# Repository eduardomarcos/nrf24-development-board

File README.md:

# NRF24 Development Board

The goal of this repository is to keep a version of a useful development boards for my [MySensors](https://www.mysensors.org/) projects based on atmega 328, esp32 and nrf24l01 module, so I do not need to wire all componentes into a breadboard.

## Atmega328 Development Board

Features:
* Almost all I/O pins available for direct connection
* Uses [3.3V Boost Buck](https://es.aliexpress.com/item/32822323191.html) for an input up to 5V (Considering that the sensor will be powered by a [TP4056](https://www.best-microcontroller-projects.com/tp4056.html) battery charger)
* If voltage regulator is wired by a connector headers instead of soldering, it would be possible to use a different voltage regulator (keep in mind that nrf24 module works with no more than ~3.6V or could be damaged)
* Internal voltage of 3.3 for the atmega 328
* NRF24L01 wired with a 10uF capacitor for noise reduction
* Reset button
* On board jumpers to disable 16 MHz crystal (and use internal 8 MHz from atmega 328)

This is the way it looks like:

## Esp32 Development Board

Features:
* All I/O pins available for direct connection
* NRF24L01 wired with an optional capacitor for noise reduction
* Err Tx and Rx led diodes for mysensors capability

This is the way it looks like:

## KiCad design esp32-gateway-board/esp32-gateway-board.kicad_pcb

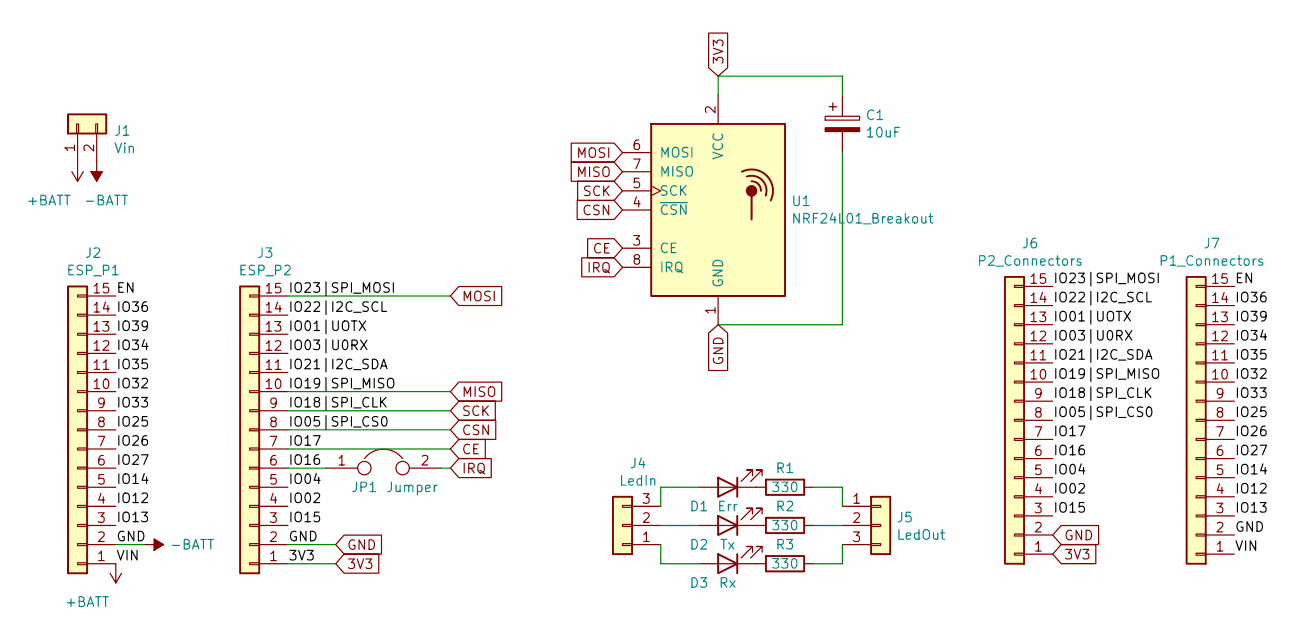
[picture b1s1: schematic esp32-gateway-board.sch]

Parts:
C1: 10uF; PinSocket_1x02_P2.54mm_Vertical
D1: Err; LED_D3.0mm
D2: Tx; LED_D3.0mm
D3: Rx; LED_D3.0mm
J1: Vin; PinSocket_1x02_P2.54mm_Vertical
J2: ESP_P1; PinSocket_1x15_P2.54mm_Vertical
J3: ESP_P2; PinSocket_1x15_P2.54mm_Vertical
J4: LedIn; PinSocket_1x03_P2.54mm_Vertical
J5: LedOut; PinSocket_1x03_P2.54mm_Vertical
J6: P2_Connectors; PinSocket_1x15_P2.54mm_Vertical
J7: P1_Connectors; PinSocket_1x15_P2.54mm_Vertical
JP1: Jumper; PinHeader_1x02_P2.54mm_Vertical
R1, R2, R3: 330; R_Axial_DIN0207_L6.3mm_D2.5mm_P10.16mm_Horizontal
U1: NRF24L01_Breakout; nRF24L01_Breakout

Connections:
3V3: C1.1, J3.1, J6.1, U1.2 (VCC)
+BATT: J1.1, J2.1, J7.1
/EN: J2.15, J7.15
/IO01|UOTX: J3.13, J6.13
/IO02: J3.4, J6.4
/IO03|U0RX: J3.12, J6.12
/IO04: J3.5, J6.5
/IO12: J2.4, J7.4
/IO13: J2.3, J7.3
/IO14: J2.5, J7.5
/IO15: J3.3, J6.3
/IO16: J3.6, J6.6, JP1.1
/IO21|I2C_SDA: J3.11, J6.11
/IO22|I2C_SCL: J3.14, J6.14
/IO25: J2.8, J7.8
/IO26: J2.7, J7.7
/IO27: J2.6, J7.6
/IO32: J2.10, J7.10
/IO33: J2.9, J7.9
/IO34: J2.12, J7.12
/IO35: J2.11, J7.11
/IO36: J2.14, J7.14
/IO39: J2.13, J7.13
CE: J3.7, J6.7, U1.3 (CE)
CSN: J3.8, J6.8, U1.4 (~CSN)
GND: C1.2, J1.2, J2.2, J3.2, J6.2, J7.2, U1.1 (GND)
MISO: J3.10, J6.10, U1.7 (MISO)
MOSI: J3.15, J6.15, U1.6 (MOSI)
unnamed: D1.1 (K), R1.2
unnamed: D1.2 (A), J4.3
unnamed: D2.1 (K), R2.2
unnamed: D2.2 (A), J4.2
unnamed: D3.1 (K), R3.2
unnamed: D3.2 (A), J4.1
unnamed: J5.1, R1.1
unnamed: J5.2, R2.1
unnamed: J5.3, R3.1
unnamed: JP1.2, U1.8 (IRQ)
SCK: J3.9, J6.9, U1.5 (SCK)

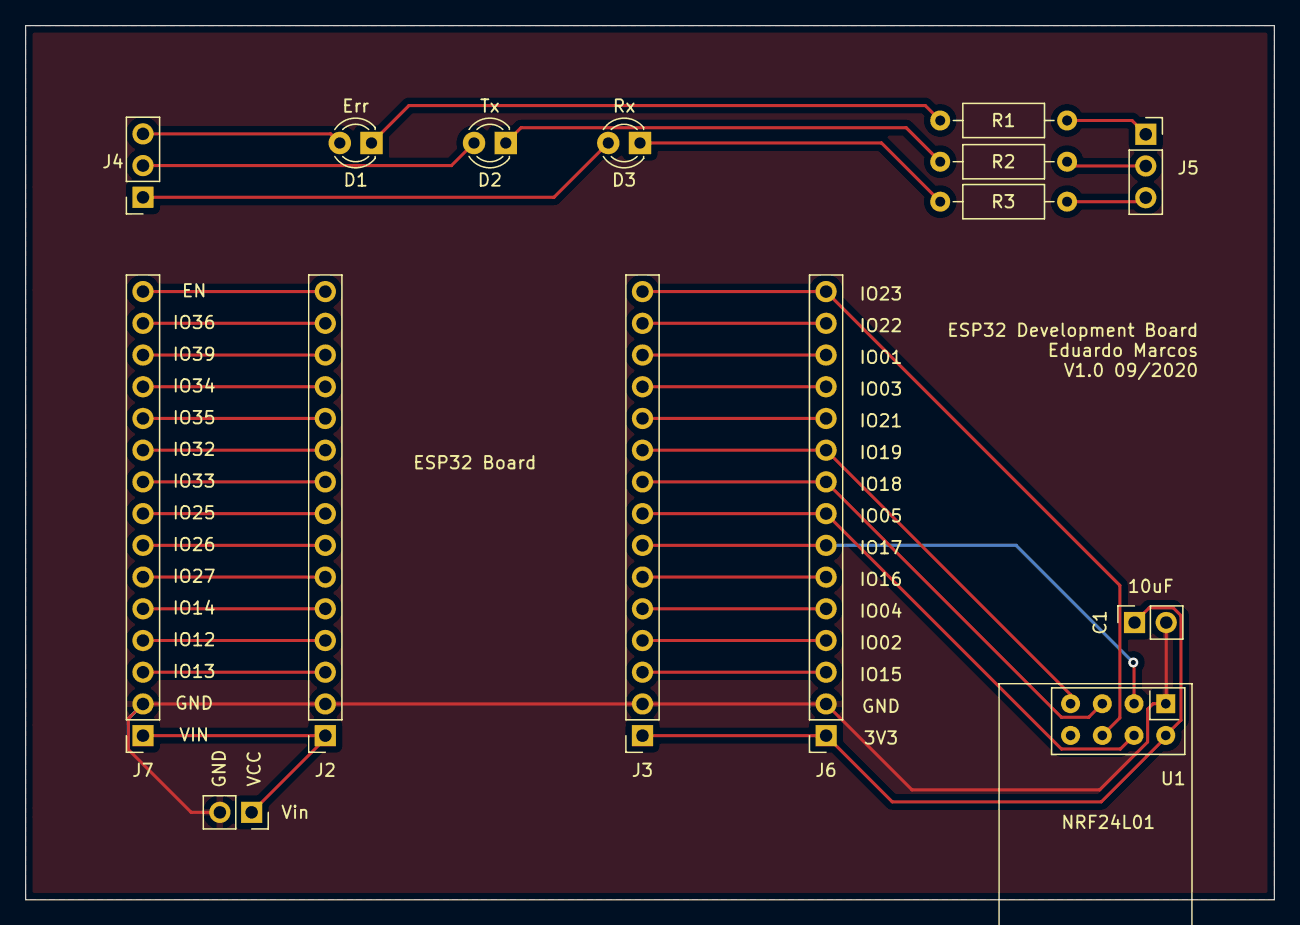
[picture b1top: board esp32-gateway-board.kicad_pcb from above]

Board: 2 copper layers, 100.0 x 70.0 mm, 15 parts (0 on the bottom side), 38 nets.

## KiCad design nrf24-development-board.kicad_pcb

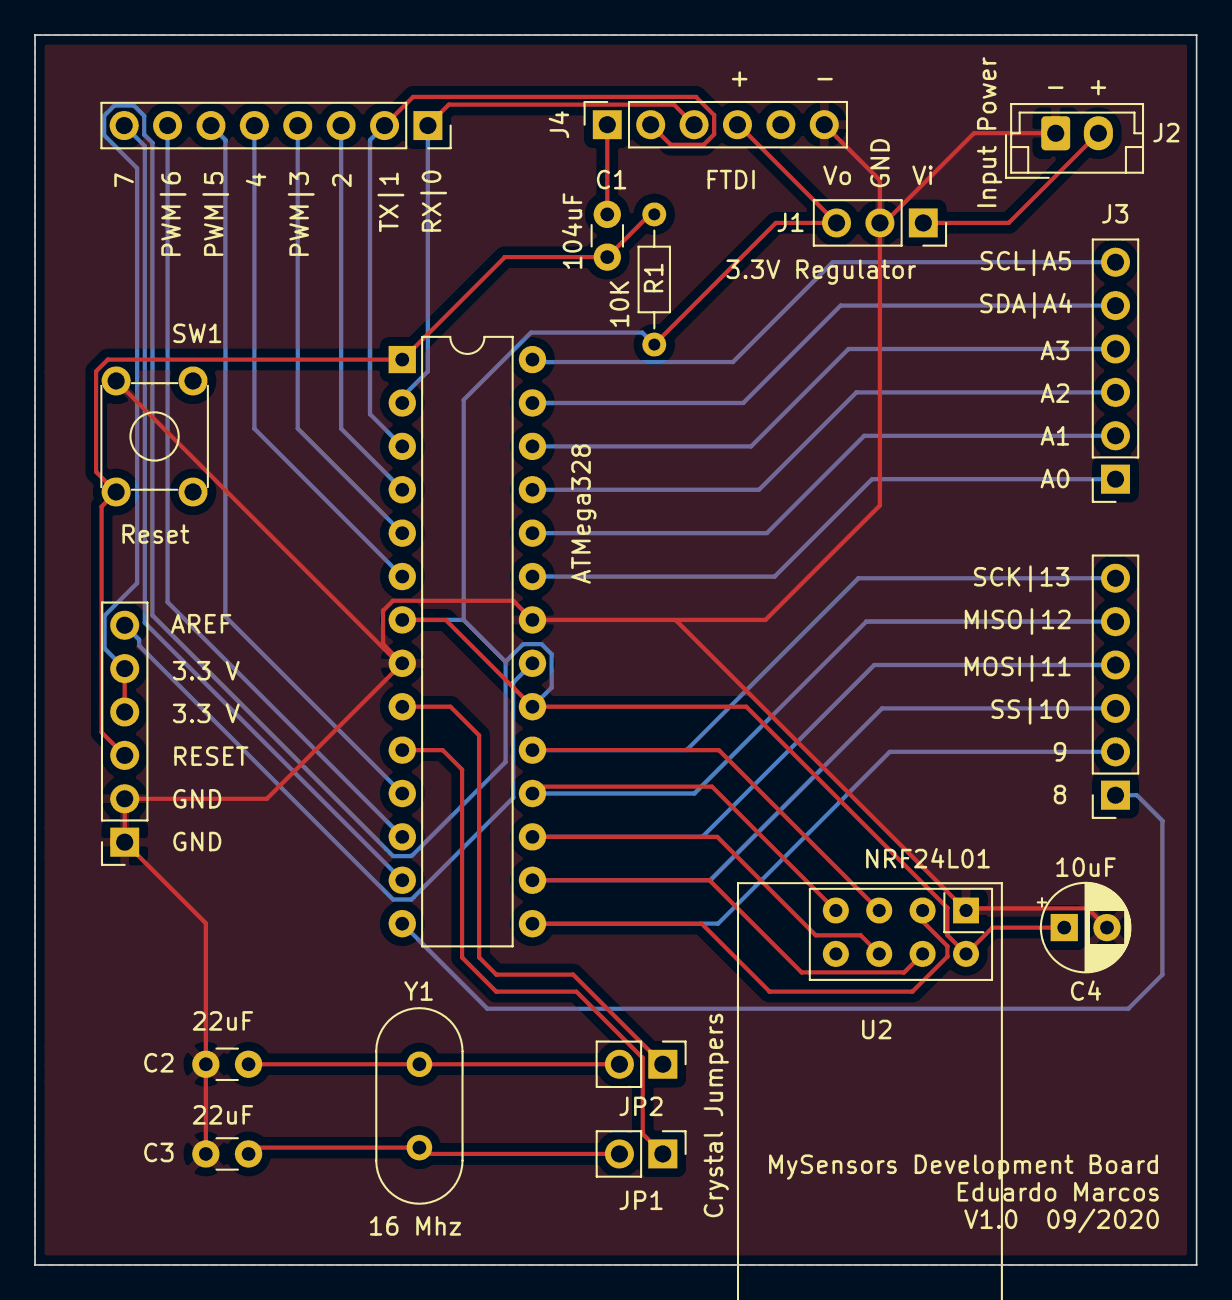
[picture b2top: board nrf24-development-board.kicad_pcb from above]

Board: 2 copper layers, 68.0 x 72.0 mm, 18 parts (0 on the bottom side), 29 nets.

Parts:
ATMega328: ATmega328P-PU; DIP-28_W7.62mm
C1: 104uF; C_Disc_D3.0mm_W1.6mm_P2.50mm
C2, C3: 22uF; C_Disc_D3.0mm_W1.6mm_P2.50mm
C4: 10uF; CP_Radial_D5.0mm_P2.50mm
J1: 3.3V Regulator; PinSocket_1x03_P2.54mm_Vertical
J2: Vin; JST_EH_B2B-EH-A_1x02_P2.50mm_Vertical
J3: Analog Connectors; PinSocket_1x06_P2.54mm_Vertical
J4: FTDI; PinSocket_1x06_P2.54mm_Vertical
J5: Digital Connectors; PinSocket_1x06_P2.54mm_Vertical
J6: Digital Connectors; PinSocket_1x08_P2.54mm_Vertical
J7: Control Connectors; PinSocket_1x06_P2.54mm_Vertical
JP1, JP2: Jumper; PinHeader_1x02_P2.54mm_Vertical
R1: 10K; R_Axial_DIN0204_L3.6mm_D1.6mm_P7.62mm_Horizontal
SW1: Reset; SW_TH_Tactile_Omron_B3F-10xx
U2: NRF24L01; nRF24L01_Breakout
Y1: 16Mhz; Crystal_HC49-4H_Vertical

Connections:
+3V3: ATMega328.7, ATMega328.20, C4.1, J1.3, J4.4, J7.4, J7.5, R1.2, U2.2
/Aref: ATMega328.21, J7.6
/DTR: C1.1, J4.1
/Rx: ATMega328.2, ATMega328.3, J4.2, J4.3, J6.1, J6.2
GND: ATMega328.8, ATMega328.22, C2.1, C3.1, C4.2, J1.2, J2.1, J4.6, J7.1, J7.2, SW1.2, U2.1
unnamed: ATMega328.1, C1.2, J7.3, R1.1, SW1.1
unnamed: ATMega328.4, J6.3
unnamed: ATMega328.5, J6.4
unnamed: ATMega328.6, J6.5
unnamed: ATMega328.9, JP2.1
unnamed: ATMega328.10, JP1.1
unnamed: ATMega328.11, J6.6
unnamed: ATMega328.12, J6.7
unnamed: ATMega328.13, J6.8
unnamed: ATMega328.14, J5.1
unnamed: ATMega328.15, J5.2, U2.3
unnamed: ATMega328.16, J5.3, U2.4
unnamed: ATMega328.17, J5.4, U2.6
unnamed: ATMega328.18, J5.5, U2.7
unnamed: ATMega328.19, J5.6, U2.5
unnamed: ATMega328.23, J3.1
unnamed: ATMega328.24, J3.2
unnamed: ATMega328.25, J3.3
unnamed: ATMega328.26, J3.4
unnamed: ATMega328.27, J3.5
unnamed: ATMega328.28, J3.6
unnamed: C2.2, JP2.2, Y1.1
unnamed: C3.2, JP1.2, Y1.2
VDC: J1.1, J2.2

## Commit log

2020-09-01 Schematics for dev board
2020-09-01 footprint for schematics
2020-09-02 pcb basic connections
2020-09-02 pcb tracks connected
2020-09-02 Pcb labeled
2020-09-02 upload preview picture of pcb
2020-09-02 update readme with pcb preview image
2020-09-02 updated readme with fetaure details
2020-09-02 moved board to atmega328 subfolder
2020-09-02 esp32 pinout
2020-09-05 esp32 gateway with pcb
2020-09-06 upload esp32-board png
2020-09-06 update schematic
